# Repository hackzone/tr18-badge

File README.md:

# tr2018-badge
Event badge for The Reality 2018

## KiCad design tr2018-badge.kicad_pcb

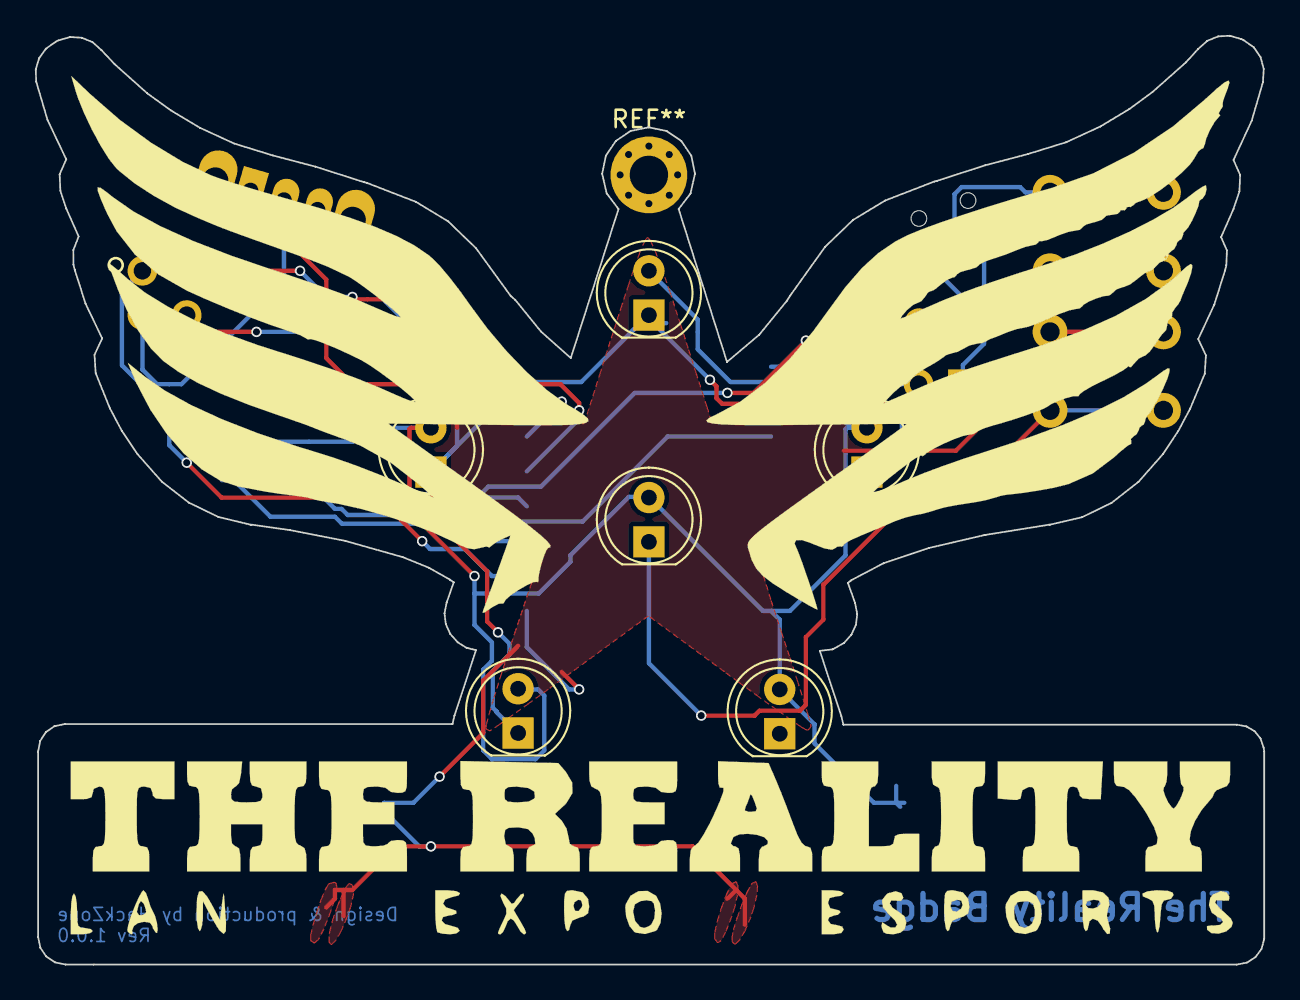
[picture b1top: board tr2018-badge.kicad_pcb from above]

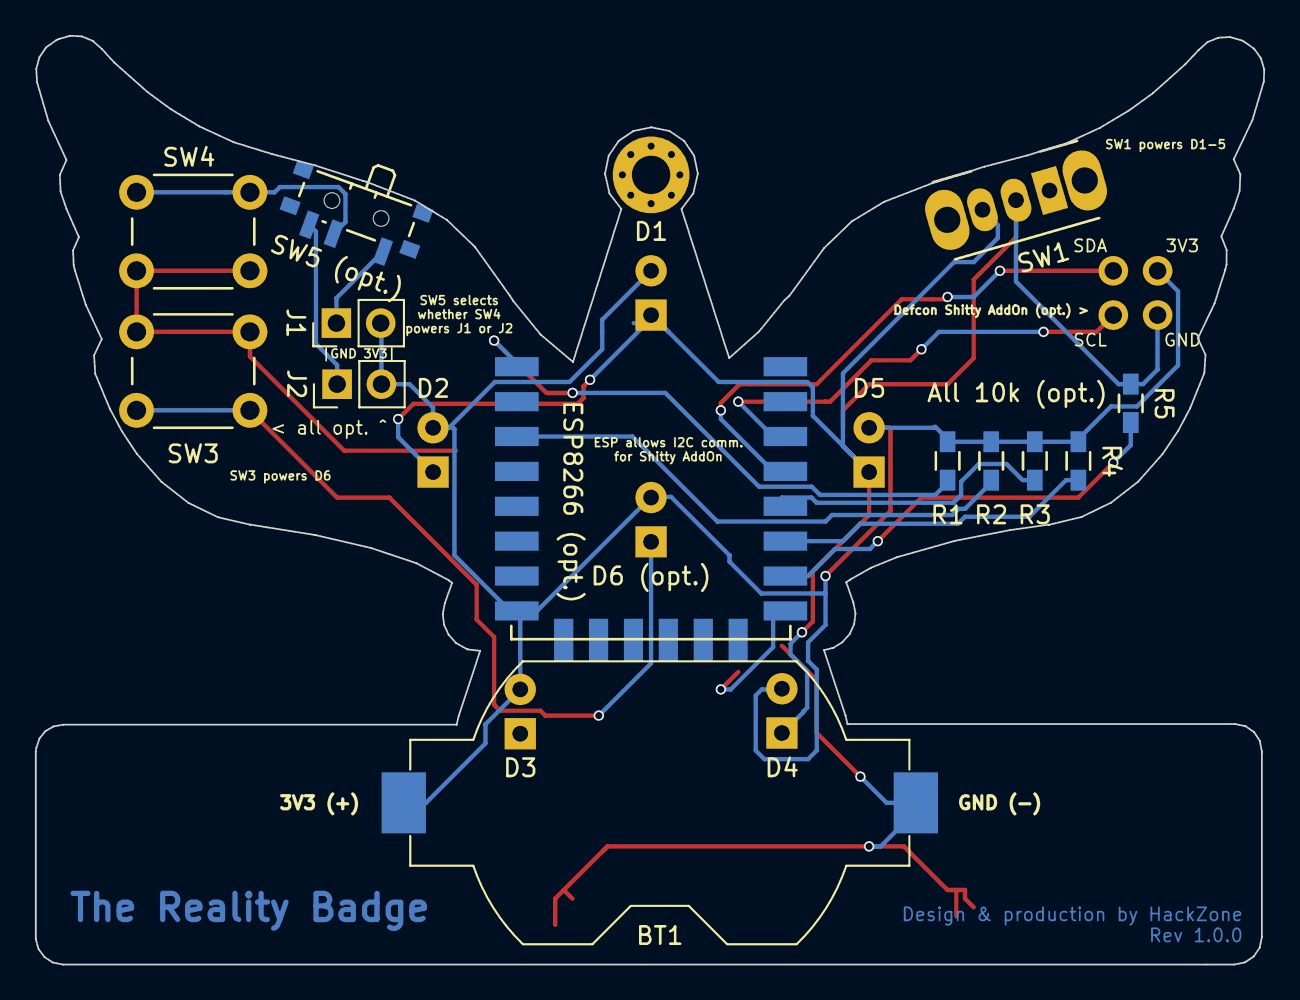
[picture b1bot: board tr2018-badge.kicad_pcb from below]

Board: 2 copper layers, 70.4 x 53.3 mm, 21 parts (13 on the bottom side), 14 nets.

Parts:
BT1: Battery_Cell; Keystone_1058_1x2032-CoinCell
D1, D2, D3, D4, D5, D6 (opt.): LED; LED_D5.0mm
J1, J2: Conn_01x02; Pin_Header_Straight_1x02_Pitch2.54mm
R1, R2, R3, R4: 10k; R_0603_HandSoldering
R5: All 10k (opt.); R_0603_HandSoldering
SW1: SW_SPDT; SW_CuK_OS102011MA1QN1_SPDT_Angled
SW3, SW4: SW_Push; SW_PUSH_6mm_h4.3mm
SW5 (opt.): SW_SPDT; SW_SPDT_PCM12
U1: ESP8266 (opt.); ESP-12E_SMD
Wings: LOGO; wingstext
X1: Defcon Shitty AddOn (opt.) >; Badgelife-Shitty-2x2

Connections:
FLASH_EN: R3.2, U1.12
GND: BT1.2, R5.1, SW1.2, SW3.1, SW4.1, U1.9, X1.2
unnamed: D1.1, D2.1, D3.1, D4.1, D5.1, SW1.3
unnamed: D6 (opt.).1, SW3.2
unnamed: J1.1, SW5 (opt.).1
unnamed: J2.1, SW5 (opt.).3
unnamed: R1.1, U1.1
unnamed: R2.1, U1.3
unnamed: R4.2, U1.11
unnamed: R5.2, U1.10
unnamed: SW4.2, SW5 (opt.).2
SCL: U1.14, X1.3
SDA: U1.13, X1.4
VCC: BT1.1, D1.2, D2.2, D3.2, D4.2, D5.2, D6 (opt.).2, J1.2, J2.2, R1.2, R2.2, R3.1, R4.1, U1.8, X1.1

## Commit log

2018-08-14 Initial fill w/ WIP badge design
2018-08-14 Updated schematic & design, added costs spreadsheet
2018-08-14 Added notes on PCB layout
2018-08-23 Cleaned up libraries
2018-08-23 Updated badge design with latest ideas
2018-08-25 Design for PCB mill prototype (w/o functional ESP + SAO)
2018-09-04 Bump to rev 1.0.0
2018-09-04 Made power bus more robust against edge cut errors
2018-09-05 Added descriptive texts, fixed LED orientation, generated gerbers
2018-09-05 Made mask subtract from silk. This version went to PCB house.
